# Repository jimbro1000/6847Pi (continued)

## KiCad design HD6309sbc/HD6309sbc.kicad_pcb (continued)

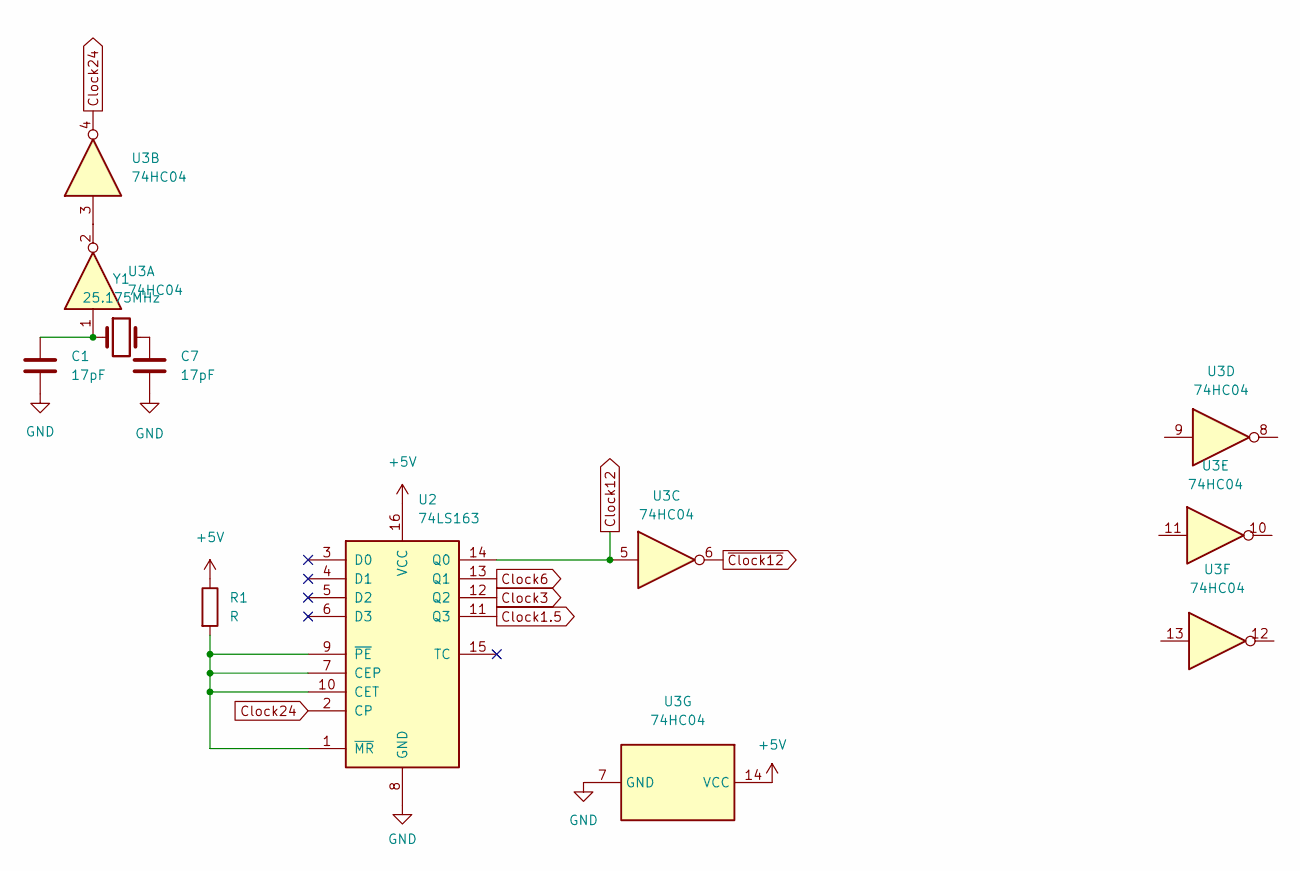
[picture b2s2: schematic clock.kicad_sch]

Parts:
C1, C7: 17pF; C_0805_2012Metric
R1: R; R_0805_2012Metric
U2: 74LS163; SO-16_3.9x9.9mm_P1.27mm
U3: 74HC04; SO-14_3.9x8.65mm_P1.27mm
Y1: 25.175MHz; Crystal_HC18-U_Vertical

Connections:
+5V: R1.1, U2.16 (VCC), U3.14 (VCC); also elsewhere on the board
Clock1.5: U2.11 (Q3)
Clock3: U2.12 (Q2); also elsewhere on the board
Clock6: U2.13 (Q1); also elsewhere on the board
Clock12: U2.14 (Q0), U3.5; also elsewhere on the board
Clock24: U2.2 (CP), U3.4; also elsewhere on the board
GND: C1.2, C7.2, U2.8 (GND), U3.7 (GND); also elsewhere on the board
unnamed: C1.1, U3.1, Y1.1
unnamed: C7.1, Y1.2
unnamed: R1.2, U2.1 (~MR), U2.7 (CEP), U2.9 (~PE), U2.10 (CET)
unnamed: U3.2, U3.3
~Clock12: U3.6; also elsewhere on the board

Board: 2 copper layers, 29 parts (0 on the bottom side), 67 nets, no tracks yet.

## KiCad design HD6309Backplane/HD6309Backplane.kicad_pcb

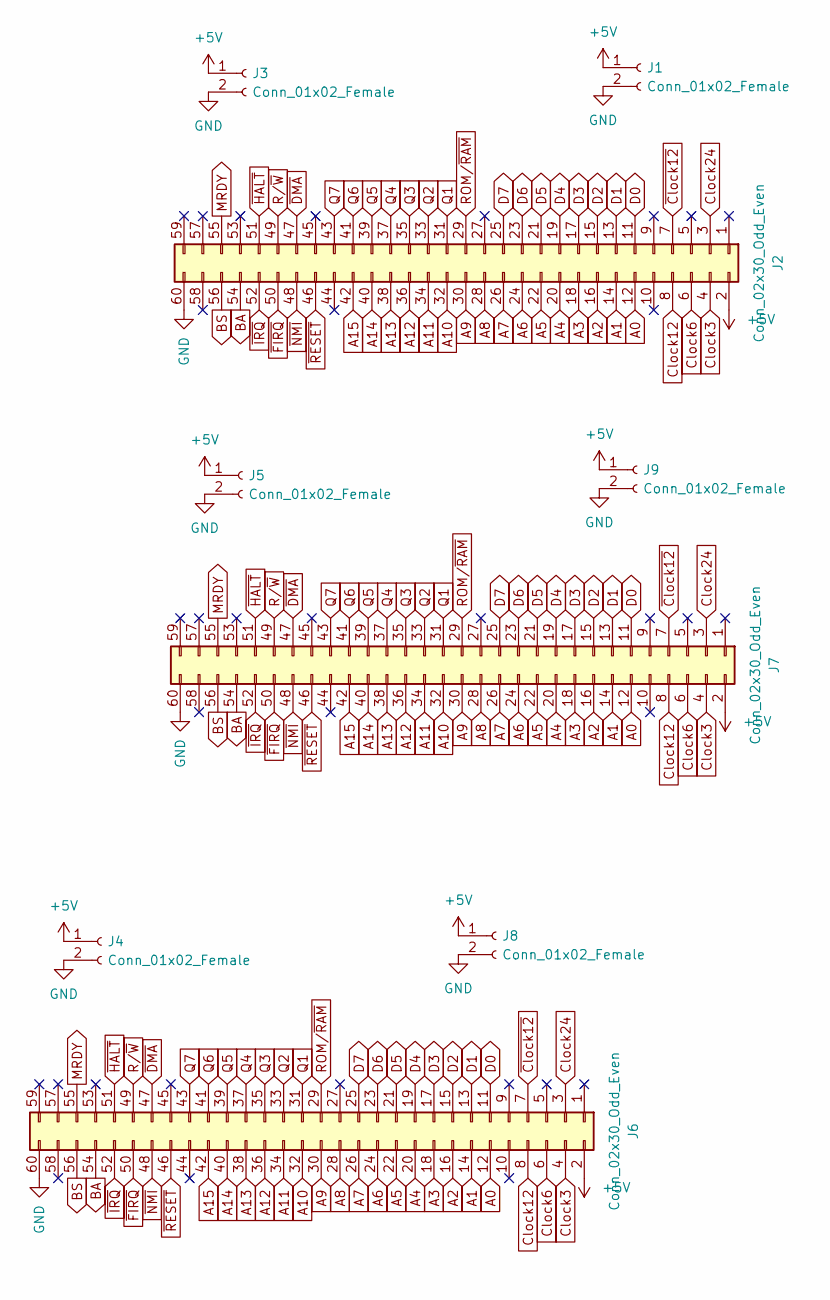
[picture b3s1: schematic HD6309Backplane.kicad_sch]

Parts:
J1, J3, J4, J5, J8, J9: Conn_01x02_Female; PinSocket_1x02_P2.54mm_Vertical
J2, J6, J7: Conn_02x30_Odd_Even; PinSocket_2x30_P2.54mm_Vertical

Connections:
+5V: J1.1, J2.2, J3.1, J4.1, J5.1, J6.2, J7.2, J8.1, J9.1
A0: J2.12, J6.12, J7.12
A1: J2.14, J6.14, J7.14
A2: J2.16, J6.16, J7.16
A3: J2.18, J6.18, J7.18
A4: J2.20, J6.20, J7.20
A5: J2.22, J6.22, J7.22
A6: J2.24, J6.24, J7.24
A7: J2.26, J6.26, J7.26
A8: J2.28, J6.28, J7.28
A9: J2.30, J6.30, J7.30
A10: J2.32, J6.32, J7.32
A11: J2.34, J6.34, J7.34
A12: J2.36, J6.36, J7.36
A13: J2.38, J6.38, J7.38
A14: J2.40, J6.40, J7.40
A15: J2.42, J6.42, J7.42
BA: J2.54, J6.54, J7.54
BS: J2.56, J6.56, J7.56
Clock3: J2.4, J6.4, J7.4
Clock6: J2.6, J6.6, J7.6
Clock12: J2.8, J6.8, J7.8
Clock24: J2.3, J6.3, J7.3
D0: J2.11, J6.11, J7.11
D1: J2.13, J6.13, J7.13
D2: J2.15, J6.15, J7.15
D3: J2.17, J6.17, J7.17
D4: J2.19, J6.19, J7.19
D5: J2.21, J6.21, J7.21
D6: J2.23, J6.23, J7.23
D7: J2.25, J6.25, J7.25
GND: J1.2, J2.60, J3.2, J4.2, J5.2, J6.60, J7.60, J8.2, J9.2
MRDY: J2.55, J6.55, J7.55
Q1: J2.31, J6.31, J7.31
Q2: J2.33, J6.33, J7.33
Q3: J2.35, J6.35, J7.35
Q4: J2.37, J6.37, J7.37
Q5: J2.39, J6.39, J7.39
Q6: J2.41, J6.41, J7.41
Q7: J2.43, J6.43, J7.43
ROM/~RAM: J2.29, J6.29, J7.29
R/~W: J2.49, J6.49, J7.49
~Clock12: J2.7, J6.7, J7.7
~DMA: J2.47, J6.47, J7.47
~FIRQ: J2.50, J6.50, J7.50
~HALT: J2.51, J6.51, J7.51
~IRQ: J2.52, J6.52, J7.52
~NMI: J2.48, J6.48, J7.48
~RESET: J2.46, J6.46, J7.46

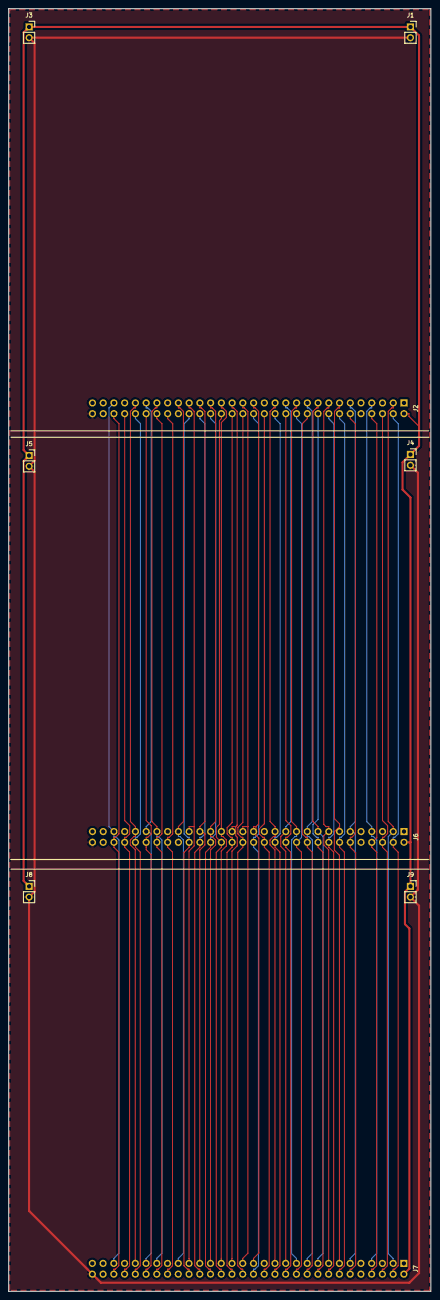
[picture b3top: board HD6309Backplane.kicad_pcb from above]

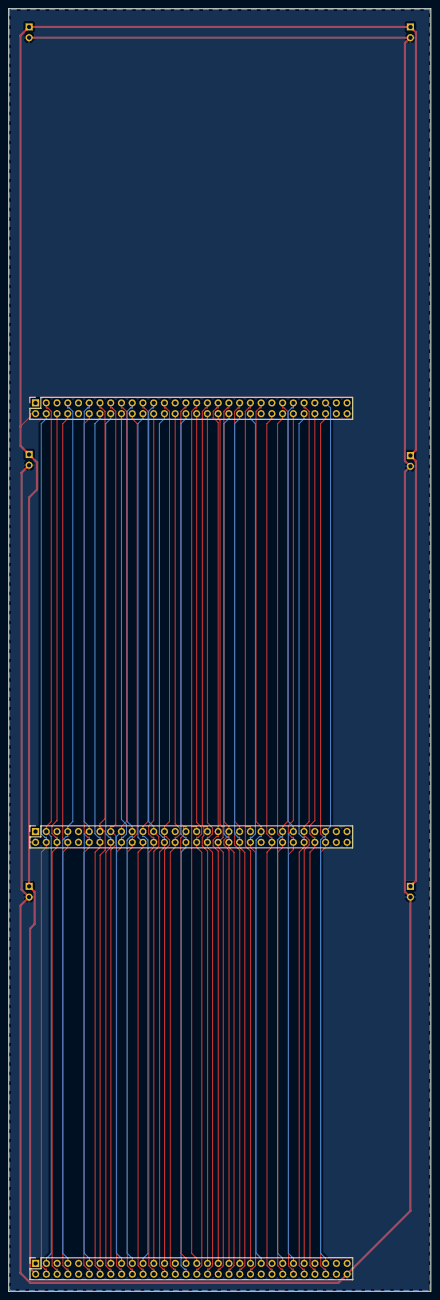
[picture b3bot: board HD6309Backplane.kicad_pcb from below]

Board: 2 copper layers, 99.8 x 303.3 mm, 9 parts (3 on the bottom side), 49 nets.

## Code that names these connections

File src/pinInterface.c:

#include "pico/stdlib.h"
//
// Created by julian on 06/04/23.
//
const uint32_t READ_DELAY = 5; //ms
const uint8_t EXT_PIN = 11; //GPIO8
const uint8_t INV_PIN = 9; //GPIO6
const uint8_t SEMI_PIN = 10; //GPIO7
const uint8_t GRAPHICS_PIN = 19; //GPIO14
const uint8_t COLOUR_SET = 22; //GPIO17
const uint8_t GM0_PIN = 11; // GPIO8
const uint8_t GM1_PIN = 12; //GPIO9
const uint8_t GM2_PIN = 14; //GPIO10
const uint8_t DATA_PIN_START = 1; //GPIO0
const uint8_t DATA_PIN_COUNT = 8; //data bus width
const uint8_t CLOCK_PIN = 20; //GPIO15
const uint8_t DA0_PIN = 22; //GPIO17
const uint8_t HS_PIN = 21; //GPIO16
const uint8_t FS_PIN = 17; //GPIO13

const int RGB_SCALE = 9;
const int RGB_PINS[9] = {22,24,25,26,27,29,31,32,34};

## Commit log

2022-02-12 Create LICENSE
2022-02-12 fix readme headings
2022-02-12 add input and output signal details
2022-02-13 Map 6847 pins to GPIO
2022-02-14 add DAC resistor ladder details
2022-02-16 add simple test code
2022-02-18 resolve misnumbered pins
2022-02-24 Expand readme for phase 2 rgb and vga
2022-02-26 add hardware design
2022-02-26 capture local c settings for vscode
2022-02-26 refine hardware layout
2022-03-02 convert row bytes to output pixels
2022-07-14 board refresh
2022-07-14 Update README.md
    Provide detail around use of AD724JR to provide composite output in phase 2 and remove the need for a phase 1 implementation
2022-07-15 add power protection
2022-07-15 correct pico footprint
2022-08-23 autorouted
2022-09-14 add 6309 project
2022-11-06 add level shift
2022-11-06 generate production
2022-12-22 switch synclines from input to output
2023-01-15 tidyup
2023-02-22 migrate to kicad7
2023-03-25 refresh code
2023-04-02 outline process
2023-04-03 provide default font handling
2023-04-03 rework pixel handling
2023-04-03 add font and palette
2023-04-03 elaborate palette control
2023-04-04 code for palette
2023-04-04 rework row handling
    outline clock timing for reads
2023-04-04 document methods
2023-04-04 provide rgb logic loop
2023-04-05 split processing between cores
    logic is outline rather than proven
2023-04-05 fix voltage level to rgb sync signals
2023-04-05 fix typo
2023-04-05 fix compile errors
2023-04-05 restructure project
2023-04-05 updated ignore def
2023-04-05 refactoring for quality
2023-04-06 better C
2023-04-06 faster semigraphics lookup fix text character generator
2023-04-07 reduced scale of semigraphics lookup
2023-04-07 refactoring
2023-04-07 use hexadecimal for bit masks
2024-07-26 upgrade to kicad 8 format
2024-07-26 route out board
2024-07-26 complete routing
2024-07-28 refine pcb routing
